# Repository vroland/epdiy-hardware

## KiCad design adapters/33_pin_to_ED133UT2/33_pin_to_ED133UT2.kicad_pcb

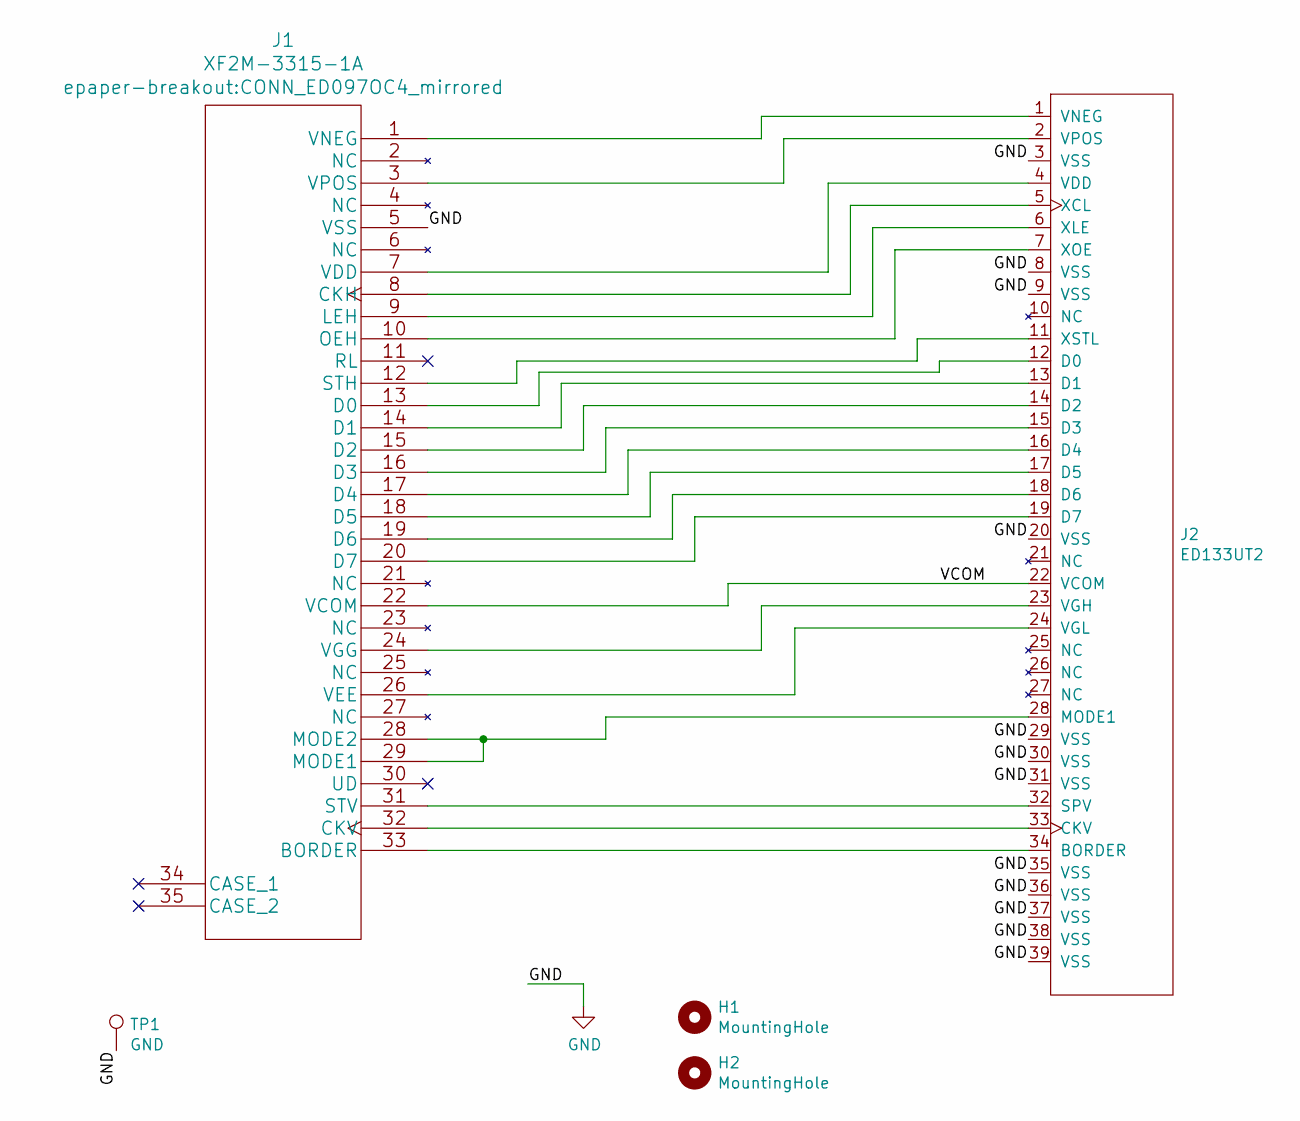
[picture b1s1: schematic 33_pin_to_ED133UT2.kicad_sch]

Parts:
H1, H2: MountingHole; MountingHole_2.2mm_M2
J1: XF2M-3315-1A; CONN_ED097OC4_mirrored
J2: ED133UT2; HRS_FH26W-39S-0.3SHW(60)
TP1: GND; TestPoint_Pad_D2.0mm

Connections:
/VCOM: J1.22 (VCOM), J2.22 (VCOM)
GND: J1.5 (VSS), J2.3 (VSS), J2.8 (VSS), J2.9 (VSS), J2.20 (VSS), J2.29 (VSS), J2.30 (VSS), J2.31 (VSS), J2.35 (VSS), J2.36 (VSS), J2.37 (VSS), J2.38 (VSS), J2.39 (VSS), TP1.1
unnamed: J1.33 (BORDER), J2.34 (BORDER)
unnamed: J1.8 (CKH), J2.5 (XCL)
unnamed: J1.32 (CKV), J2.33 (CKV)
unnamed: J1.13 (D0), J2.12 (D0)
unnamed: J1.14 (D1), J2.13 (D1)
unnamed: J1.15 (D2), J2.14 (D2)
unnamed: J1.16 (D3), J2.15 (D3)
unnamed: J1.17 (D4), J2.16 (D4)
unnamed: J1.18 (D5), J2.17 (D5)
unnamed: J1.19 (D6), J2.18 (D6)
unnamed: J1.20 (D7), J2.19 (D7)
unnamed: J1.9 (LEH), J2.6 (XLE)
unnamed: J1.28 (MODE2), J1.29 (MODE1), J2.28 (MODE1)
unnamed: J1.10 (OEH), J2.7 (XOE)
unnamed: J1.12 (STH), J2.11 (XSTL)
unnamed: J1.31 (STV), J2.32 (SPV)
unnamed: J1.7 (VDD), J2.4 (VDD)
unnamed: J1.26 (VEE), J2.24 (VGL)
unnamed: J1.24 (VGG), J2.23 (VGH)
unnamed: J1.1 (VNEG), J2.1 (VNEG)
unnamed: J1.3 (VPOS), J2.2 (VPOS)

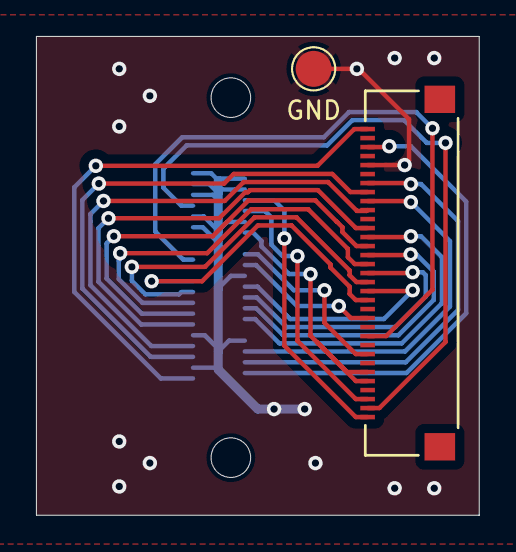
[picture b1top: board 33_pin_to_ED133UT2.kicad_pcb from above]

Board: 2 copper layers, 24.6 x 26.6 mm, 5 parts (1 on the bottom side), 23 nets.

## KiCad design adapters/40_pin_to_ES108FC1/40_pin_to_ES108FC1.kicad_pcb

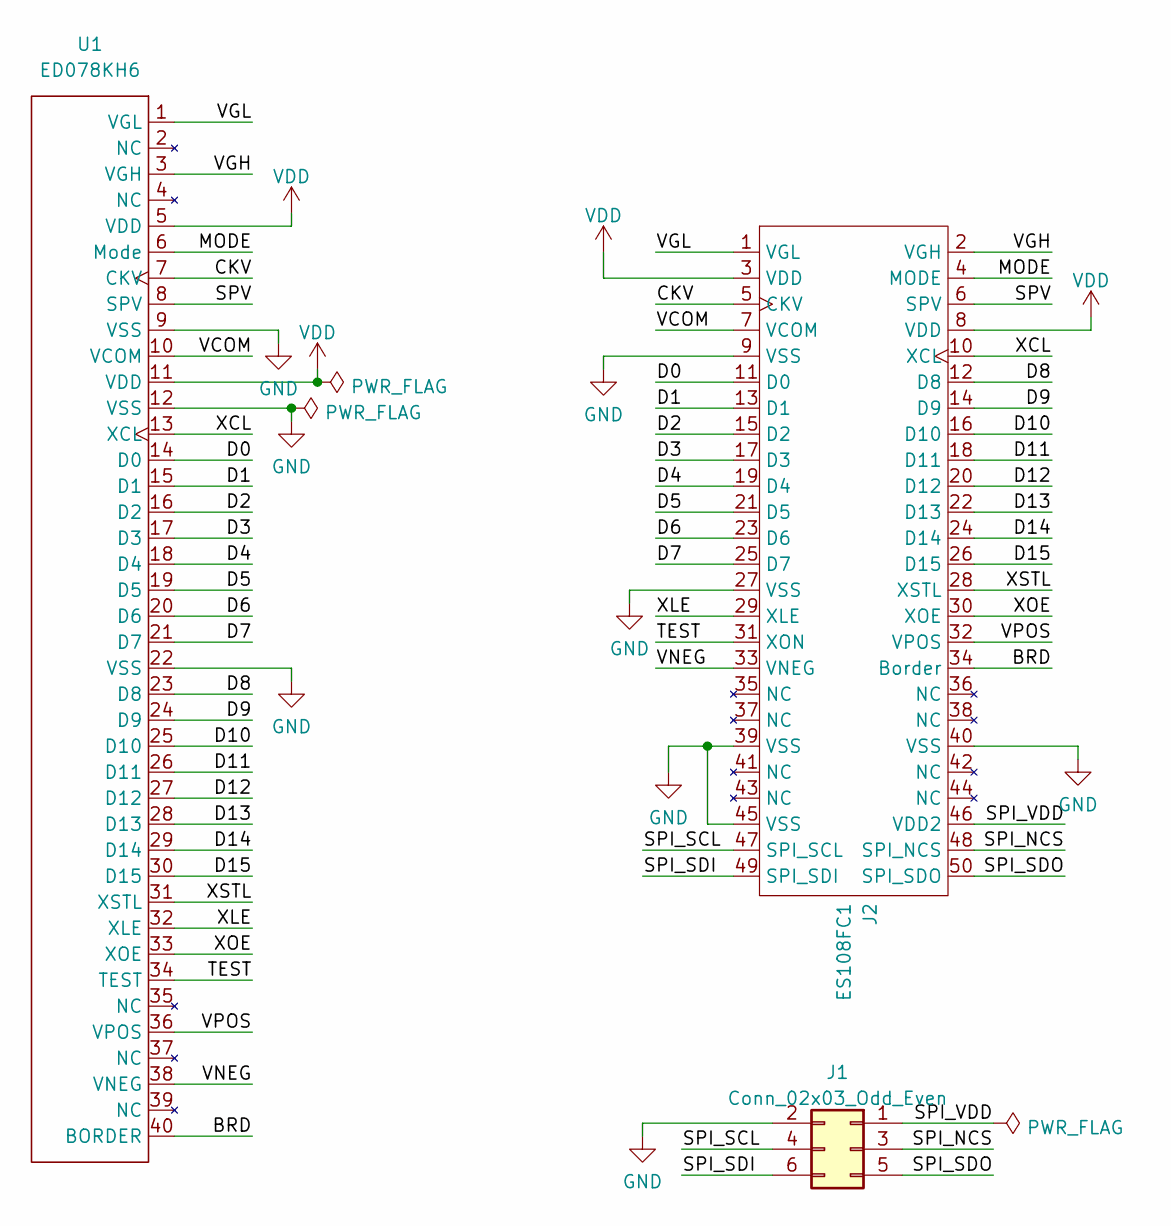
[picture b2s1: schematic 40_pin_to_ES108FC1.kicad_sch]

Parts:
J1: Conn_02x03_Odd_Even; PinHeader_2x03_P2.54mm_Vertical
J2: ES108FC1; LCSC C2880696
U1: ED078KH6; Hirose_FH12-40S-0.5SH_mirrored; LCSC C202114

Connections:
/BRD: J2.34 (Border), U1.40 (BORDER)
/CKV: J2.5 (CKV), U1.7 (CKV)
/D0: J2.11 (D0), U1.14 (D0)
/D1: J2.13 (D1), U1.15 (D1)
/D2: J2.15 (D2), U1.16 (D2)
/D3: J2.17 (D3), U1.17 (D3)
/D4: J2.19 (D4), U1.18 (D4)
/D5: J2.21 (D5), U1.19 (D5)
/D6: J2.23 (D6), U1.20 (D6)
/D7: J2.25 (D7), U1.21 (D7)
/D8: J2.12 (D8), U1.23 (D8)
/D9: J2.14 (D9), U1.24 (D9)
/D10: J2.16 (D10), U1.25 (D10)
/D11: J2.18 (D11), U1.26 (D11)
/D12: J2.20 (D12), U1.27 (D12)
/D13: J2.22 (D13), U1.28 (D13)
/D14: J2.24 (D14), U1.29 (D14)
/D15: J2.26 (D15), U1.30 (D15)
/MODE: J2.4 (MODE), U1.6 (Mode)
/SPI_NCS: J1.3, J2.48 (SPI_NCS)
/SPI_SCL: J1.4, J2.47 (SPI_SCL)
/SPI_SDI: J1.6, J2.49 (SPI_SDI)
/SPI_SDO: J1.5, J2.50 (SPI_SDO)
/SPI_VDD: J1.1, J2.46 (VDD2)
/SPV: J2.6 (SPV), U1.8 (SPV)
/TEST: J2.31 (XON), U1.34 (TEST)
/VCOM: J2.7 (VCOM), U1.10 (VCOM)
/VGH: J2.2 (VGH), U1.3 (VGH)
/VGL: J2.1 (VGL), U1.1 (VGL)
/VNEG: J2.33 (VNEG), U1.38 (VNEG)
/VPOS: J2.32 (VPOS), U1.36 (VPOS)
/XCL: J2.10 (XCL), U1.13 (XCL)
/XLE: J2.29 (XLE), U1.32 (XLE)
/XOE: J2.30 (XOE), U1.33 (XOE)
/XSTL: J2.28 (XSTL), U1.31 (XSTL)
GND: J1.2, J2.9 (VSS), J2.27 (VSS), J2.39 (VSS), J2.40 (VSS), J2.45 (VSS), U1.9 (VSS), U1.12 (VSS), U1.22 (VSS)
VDD: J2.3 (VDD), J2.8 (VDD), U1.5 (VDD), U1.11 (VDD)

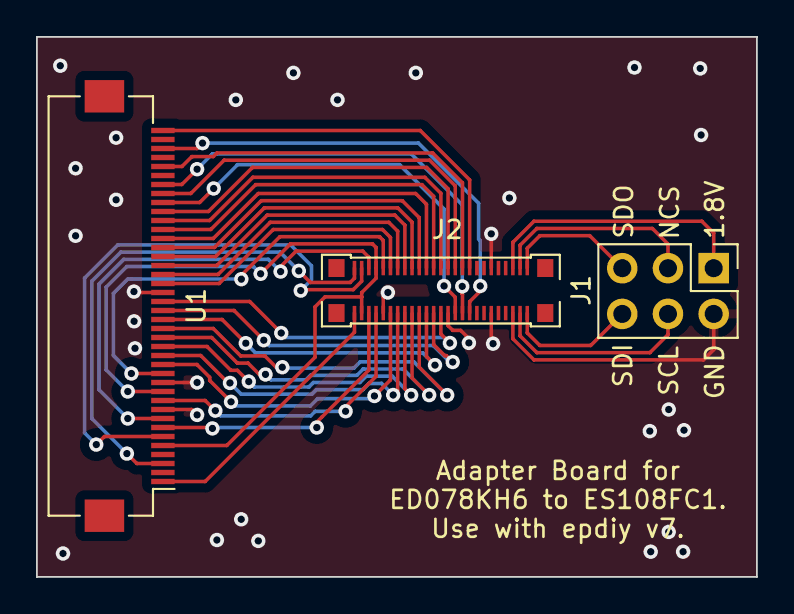
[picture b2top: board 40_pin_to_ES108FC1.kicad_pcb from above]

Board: 2 copper layers, 40.0 x 30.0 mm, 3 parts (0 on the bottom side), 37 nets.

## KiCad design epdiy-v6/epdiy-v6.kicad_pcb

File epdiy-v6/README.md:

### Epdiy V6

Uses the TPS65185 IC for power delivery instead of the previous design and drops the ED060SC7 connector,
but adds additional available GPIOs though a GPIO expander.

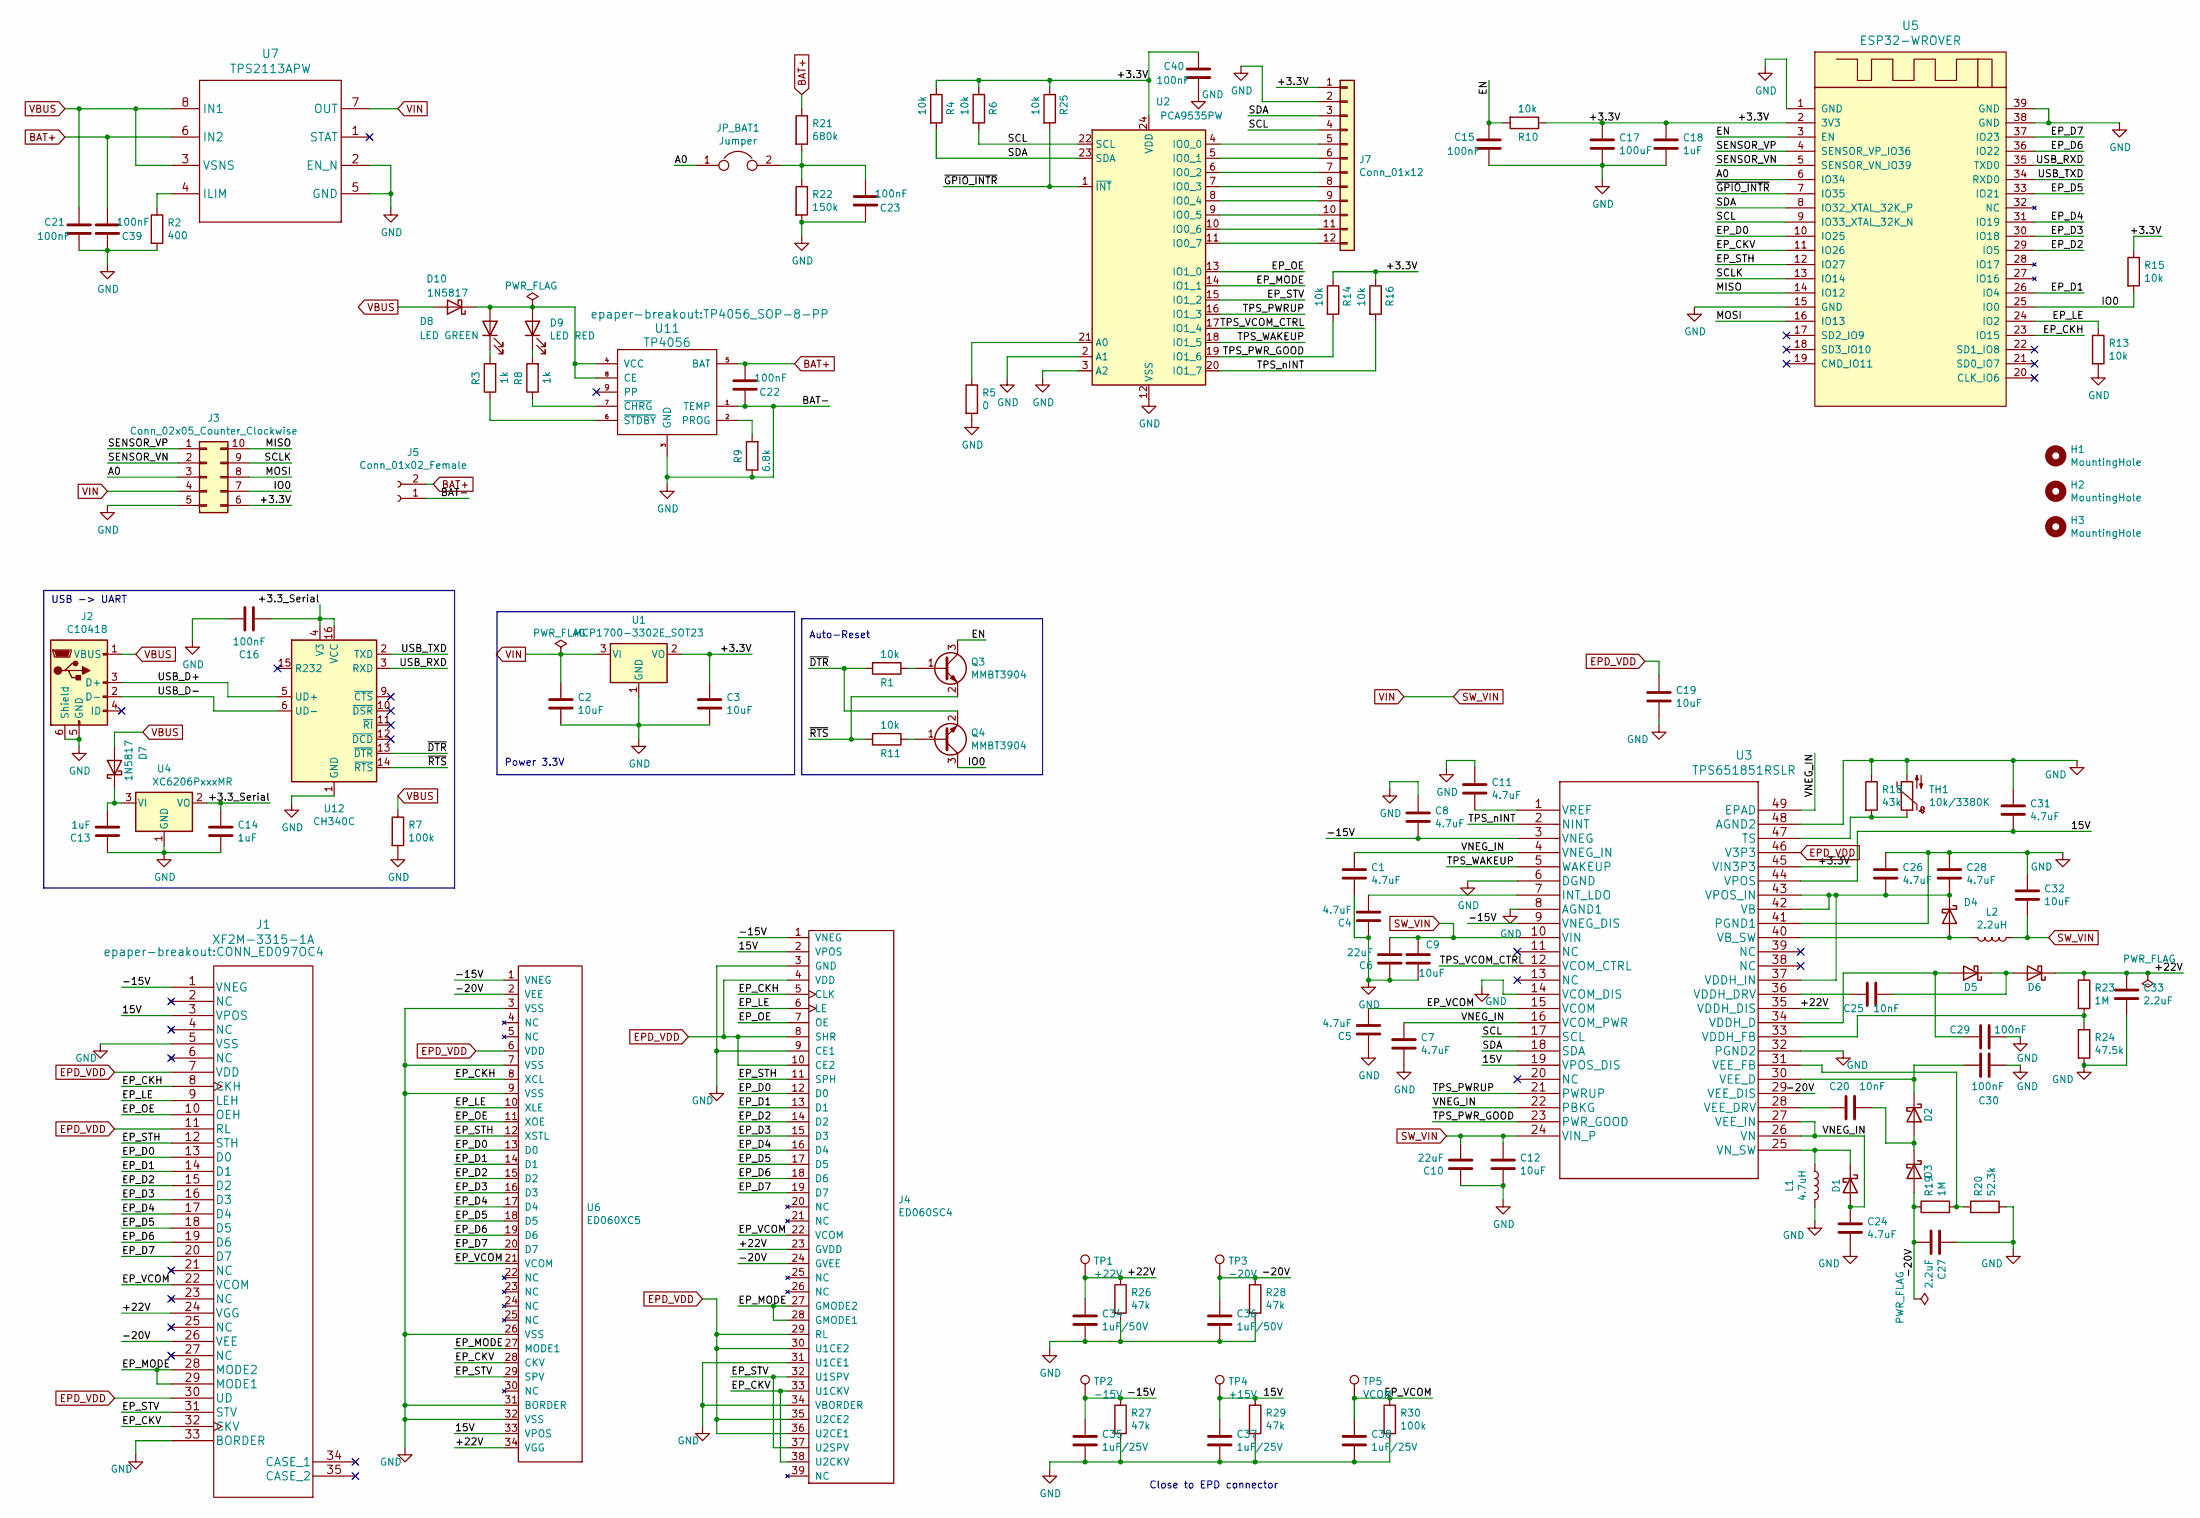
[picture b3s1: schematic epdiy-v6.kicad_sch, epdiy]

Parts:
C1, C4, C5, C7, C8, C11, C24, C26, C28, C31: 4.7uF; C_0805_2012Metric; LCSC C1779
C2, C3, C9, C12, C32: 10uF; C_0805_2012Metric; LCSC C15850
C6, C10: 22uF; C_0805_2012Metric; LCSC C45783
C13, C14, C18: 1uF; C_0805_2012Metric; LCSC C28323
C15, C16, C21, C22, C23, C29, C30, C39, C40: 100nF; C_0805_2012Metric; LCSC C49678
C17: 100uF; CP_EIA-3528-15_AVX-H; LCSC C16133
C19: 10uF; C_0805_2012Metric; LCSC C19702
C20, C25: 10nF; C_0805_2012Metric; LCSC C1710
C27, C33: 2.2uF; C_0805_2012Metric; LCSC C49217
C34, C36: 1uF/50V; C_1206_3216Metric; LCSC C1848
C35, C37, C38: 1uF/25V; C_0805_2012Metric; LCSC C28323
D1, D2, D3, D4, D5, D6: MBR0540; D_SOD-123; LCSC C21353
D7, D10: 1N5817; D_SOD-123; LCSC C8598
D8: LED GREEN; LED_0805_2012Metric; LCSC C2297
D9: LED RED; LED_0805_2012Metric; LCSC C84256
H1, H2, H3: MountingHole; MountingHole_2.2mm_M2
J1: XF2M-3315-1A; CONN_ED097OC4; LCSC C231420
J2: C10418; USB_Micro-B_A01SB141B1-067; LCSC C10418
J3: Conn_02x05_Counter_Clockwise; PinHeader_2x05_P2.54mm_Vertical
J4: ED060SC4; HRS_FH26W-39S-0.3SHW(60); LCSC C519255
J5: Conn_01x02_Female; PinHeader_1x02_P2.54mm_Vertical
J7: Conn_01x12; PinHeader_2x06_P2.54mm_Vertical
JP_BAT1: Jumper; SolderJumper-2_P1.3mm_Bridged2Bar_RoundedPad1.0x1.5mm
L1: 4.7uH; L_Taiyo-Yuden_NR-50xx_HandSoldering; LCSC C222947
L2: 2.2uH; L_Taiyo-Yuden_NR-40xx_HandSoldering; LCSC C92959
Q3, Q4: MMBT3904; SOT-23; LCSC C20526
R1, R4, R6, R10, R11, R13, R14, R15, R16, R25: 10k; R_0603_1608Metric; LCSC C25804
R2: 400; R_0603_1608Metric; LCSC C23151
R3, R8: 1k; R_0603_1608Metric; LCSC C21190
R5: 0; R_0603_1608Metric
R7, R30: 100k; R_0603_1608Metric; LCSC C25803
R9: 6.8k; R_0603_1608Metric; LCSC C23212
R18: 43k; R_0603_1608Metric; LCSC C23172
R19, R23: 1M; R_0603_1608Metric; LCSC C22935
R20: 52.3k; R_0603_1608Metric; LCSC C23196
R21: 680k; R_0603_1608Metric; LCSC C25822
R22: 150k; R_0603_1608Metric; LCSC C22807
R24: 47.5k; R_0603_1608Metric; LCSC C25819
R26, R27, R28, R29: 47k; R_0603_1608Metric; LCSC C25819
TH1: 10k/3380K; R_0603_1608Metric; LCSC C76589
TP1: +22V; TestPoint_Pad_D2.5mm
TP2: -15V; TestPoint_Pad_D2.5mm
TP3: -20V; TestPoint_Pad_D2.5mm
TP4: +15V; TestPoint_Pad_D2.5mm
TP5: VCOM; TestPoint_Pad_D2.5mm
U1: MCP1700-3302E_SOT23; SOT-23; LCSC C39051
U2: PCA9535PW; TSSOP-24_4.4x7.8mm_P0.65mm; LCSC C255606
U3: TPS651851RSLR; LCSC C139292
U4: XC6206PxxxMR; SOT-23; LCSC C5446
U5: ESP32-WROVER; LCSC C503591
U6: ED060XC5; X05A20H34G; LCSC C528053
U7: TPS2113APW; LCSC C130052
U11: TP4056; TP4056_SOP-8-PP; LCSC C16581
U12: CH340C; SOIC-16_3.9x9.9mm_P1.27mm; LCSC C84681

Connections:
/15V: C31.2, C37.1, J1.3 (VPOS), J4.2 (VPOS), R29.1, TP4.1, U3.19 (VPOS_DIS), U3.44 (VPOS), U6.33 (VPOS)
/+3.3V: C3.2, C17.1, C18.2, C40.1, J3.6, J7.1, R4.1, R6.1, R10.1, R14.1, R15.1, R16.1, R25.1, U1.2 (VO), U2.24 (VDD), U3.45 (VIN3P3), U5.2 (3V3)
/+3.3_Serial: C14.2, C16.1, U4.2 (VO), U12.4 (V3), U12.16 (VCC)
/+22V: C33.1, C34.1, D6.1 (K), J1.24 (VGG), J4.23 (GVDD), R23.1, R26.1, TP1.1, U3.35 (VDDH_DIS), U6.34 (VGG)
/-15V: C8.2, C35.1, J1.1 (VNEG), J4.1 (VNEG), R27.1, TP2.1, U3.3 (VNEG), U3.9 (VNEG_DIS), U6.1 (VNEG)
/-20V: C27.2, C36.1, D3.2 (A), J1.26 (VEE), J4.24 (GVEE), R19.1, R28.1, TP3.1, U3.29 (VEE_DIS), U6.2 (VEE)
/A0: J3.3, JP_BAT1.1, U5.6 (IO34)
/EN: C15.1, Q3.3 (C), R10.2, U5.3 (EN)
/EP_CKH: J1.8 (CKH), J4.5 (CLK), U5.23 (IO15), U6.8 (XCL)
/EP_CKV: J1.32 (CKV), J4.33 (U1CKV), J4.38 (U2CKV), U5.11 (IO26), U6.28 (CKV)
/EP_D0: J1.13 (D0), J4.12 (D0), U5.10 (IO25), U6.13 (D0)
/EP_D1: J1.14 (D1), J4.13 (D1), U5.26 (IO4), U6.14 (D1)
/EP_D2: J1.15 (D2), J4.14 (D2), U5.29 (IO5), U6.15 (D2)
/EP_D3: J1.16 (D3), J4.15 (D3), U5.30 (IO18), U6.16 (D3)
/EP_D4: J1.17 (D4), J4.16 (D4), U5.31 (IO19), U6.17 (D4)
/EP_D5: J1.18 (D5), J4.17 (D5), U5.33 (IO21), U6.18 (D5)
/EP_D6: J1.19 (D6), J4.18 (D6), U5.36 (IO22), U6.19 (D6)
/EP_D7: J1.20 (D7), J4.19 (D7), U5.37 (IO23), U6.20 (D7)
/EP_LE: J1.9 (LEH), J4.6 (LE), R13.1, U5.24 (IO2), U6.10 (XLE)
/EP_MODE: J1.28 (MODE2), J1.29 (MODE1), J4.27 (GMODE2), J4.28 (GMODE1), U2.14 (IO1_1), U6.27 (MODE1)
/EP_OE: J1.10 (OEH), J4.7 (OE), U2.13 (IO1_0), U6.11 (XOE)
/EP_STH: J1.12 (STH), J4.11 (SPH), U5.12 (IO27), U6.12 (XSTL)
/EP_STV: J1.31 (STV), J4.32 (U1SPV), J4.37 (U2SPV), U2.15 (IO1_2), U6.29 (SPV)
/EP_VCOM: C5.2, C38.1, J1.22 (VCOM), J4.22 (VCOM), R30.1, TP5.1, U3.15 (VCOM), U6.21 (VCOM)
/IO0: J3.7, Q4.3 (C), R15.2, U5.25 (IO0)
/MISO: J3.10, U5.14 (IO12)
/MOSI: J3.8, U5.16 (IO13)
/SCL: J7.4, R6.2, U2.22 (SCL), U3.17 (SCL), U5.9 (IO33_XTAL_32K_N)
/SCLK: J3.9, U5.13 (IO14)
/SDA: J7.3, R4.2, U2.23 (SDA), U3.18 (SDA), U5.8 (IO32_XTAL_32K_P)
/SENSOR_VN: J3.2, U5.5 (SENSOR_VN_IO39)
/SENSOR_VP: J3.1, U5.4 (SENSOR_VP_IO36)
/TPS_PWRUP: U2.16 (IO1_3), U3.21 (PWRUP)
/TPS_PWR_GOOD: R14.2, U2.19 (IO1_6), U3.23 (PWR_GOOD)
/TPS_VCOM_CTRL: U2.17 (IO1_4), U3.12 (VCOM_CTRL)
/TPS_WAKEUP: U2.18 (IO1_5), U3.5 (WAKEUP)
/TPS_nINT: R16.2, U2.20 (IO1_7), U3.2 (NINT)
/USB_D+: J2.3 (D+), U12.5 (UD+)
/USB_D-: J2.2 (D-), U12.6 (UD-)
/USB_RXD: U5.35 (TXD0), U12.3 (RXD)
/USB_TXD: U5.34 (RXD0), U12.2 (TXD)
/VNEG_IN: C1.1, C7.1, C24.1, D1.2 (A), U3.4 (VNEG_IN), U3.16 (VCOM_PWR), U3.22 (PBKG), U3.26 (VN), U3.27 (VEE_IN), U3.49 (EPAD)
/~DTR: Q4.2 (E), R1.2, U12.13 (~DTR)
/~GPIO_INTR: R25.2, U2.1 (~INT), U5.7 (IO35)
/~RTS: Q3.2 (E), R11.2, U12.14 (~RTS)
BAT+: C22.2, C39.2, J5.2, R21.1, U7.6 (IN2), U11.5 (BAT)
EPD_VDD: C19.1, J1.7 (VDD), J1.11 (RL), J1.30 (UD), J4.4 (VDD), J4.8 (SHR), J4.10 (CE2), J4.29 (RL), J4.30 (U1CE2), J4.35 (U2CE2), J4.36 (U2CE1), U3.46 (V3P3), U6.6 (VDD)
GND: C1.2, C2.1, C3.1, C4.1, C5.1, C6.1, C7.2, C8.1, C9.2, C10.1, C11.1, C12.2, C13.2, C14.1, C15.2, C16.2, C17.2, C18.1, C19.2, C21.2, C22.1, C23.1, C24.2, C26.1, C27.1, C28.1, C29.1, C30.2, C31.1, C32.1, C33.2, C34.2, C35.2, C36.2, C37.2, C38.2, C39.1, C40.2, J1.5 (VSS), J1.33 (BORDER), J2.5 (GND), J2.6 (Shield), J3.5, J4.3 (GND), J4.9 (CE1), J4.31 (U1CE1), J4.34 (VBORDER), J5.1, J7.2, L1.2, R2.2, R5.2, R7.2, R9.1, R13.2, R18.1, R20.2, R22.2, R24.2, R26.2, R27.2, R28.2, R29.2, R30.2, TH1.2, U1.1 (GND), U2.2 (A1), U2.3 (A2), U2.12 (VSS), U3.6 (DGND), U3.8 (AGND1), U3.14 (VCOM_DIS), U3.32 (PGND2), U3.41 (PGND1), U3.48 (AGND2), U4.1 (GND), U5.1 (GND), U5.15 (GND), U5.38 (GND), U5.39 (GND), U6.3 (VSS), U6.7 (VSS), U6.9 (VSS), U6.26 (VSS), U6.31 (BORDER), U6.32 (VSS), U7.2 (EN_N), U7.5 (GND), U11.1 (TEMP), U11.3 (GND), U12.1 (GND)
unnamed: C23.2, JP_BAT1.2, R21.2, R22.1
unnamed: D1.1 (K), L1.1, U3.25 (VN_SW)
unnamed: C20.1, D2.2 (A), D3.1 (K)
unnamed: C30.1, D2.1 (K), U3.30 (VEE_D)
unnamed: D4.2 (A), L2.2, U3.40 (VB_SW)
unnamed: C26.2, C28.2, D4.1 (K), U3.37 (VDDH_IN), U3.42 (VB), U3.43 (VPOS_IN)
unnamed: C29.2, D5.2 (A), U3.34 (VDDH_D)
unnamed: C25.1, D5.1 (K), D6.2 (A)
unnamed: C13.1, D7.1 (K), U4.3 (VI)
unnamed: D8.1 (K), R3.2
unnamed: D9.1 (K), R8.2
unnamed: D8.2 (A), D9.2 (A), D10.1 (K), U11.4 (VCC), U11.8 (CE)
unnamed: J7.5, U2.4 (IO0_0)
unnamed: J7.6, U2.5 (IO0_1)
unnamed: J7.7, U2.6 (IO0_2)
unnamed: J7.8, U2.7 (IO0_3)
unnamed: J7.9, U2.8 (IO0_4)
unnamed: J7.10, U2.9 (IO0_5)
unnamed: J7.11, U2.10 (IO0_6)
unnamed: J7.12, U2.11 (IO0_7)
unnamed: Q3.1 (B), R1.1
unnamed: Q4.1 (B), R11.1
unnamed: R5.1, U2.21 (A0)
unnamed: C4.2, U3.7 (INT_LDO)
unnamed: R18.2, TH1.1, U3.47 (TS)
unnamed: C25.2, U3.36 (VDDH_DRV)
unnamed: R23.2, R24.1, U3.33 (VDDH_FB)
unnamed: C20.2, U3.28 (VEE_DRV)
unnamed: R19.2, R20.1, U3.31 (VEE_FB)
unnamed: C11.2, U3.1 (VREF)
unnamed: R2.1, U7.4 (ILIM)
unnamed: R9.2, U11.2 (PROG)
unnamed: R8.1, U11.7 (~CHRG)
unnamed: R3.1, U11.6 (~STDBY)
SW_VIN: C2.2, C6.2, C9.1, C10.2, C12.1, C32.2, J3.4, L2.1, U1.3 (VI), U3.10 (VIN), U3.24 (VIN_P), U7.7 (OUT)
VBUS: C21.1, D7.2 (A), D10.2 (A), J2.1 (VBUS), R7.1, U7.3 (VSNS), U7.8 (IN1)

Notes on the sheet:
Close to EPD connector
Auto-Reset
USB -> UART
Power 3.3V

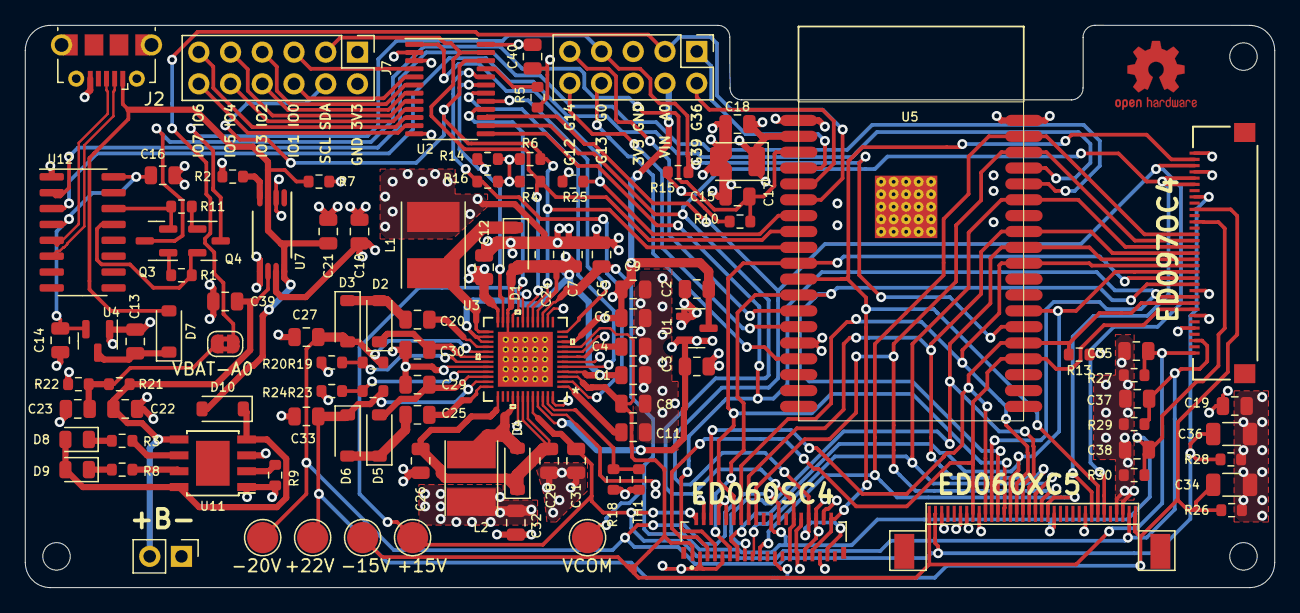
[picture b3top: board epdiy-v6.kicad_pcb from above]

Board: 4 copper layers, 100.0 x 45.0 mm, 108 parts (1 on the bottom side), 84 nets.

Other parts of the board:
CC: Symbol_CreativeCommons_SilkScreenTop_Type2_Big

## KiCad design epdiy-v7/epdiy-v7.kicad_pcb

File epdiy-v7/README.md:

### Epdiy V7

The V7 controller iteration is based on the ESP32S3. Highlights of the new board include:

- Support for high-resolution displays with 16 data lines
- Much faster updates thanks to the ESP32S3 SOC and the LCD peripheral
- An on-board RTC, LiPo charging

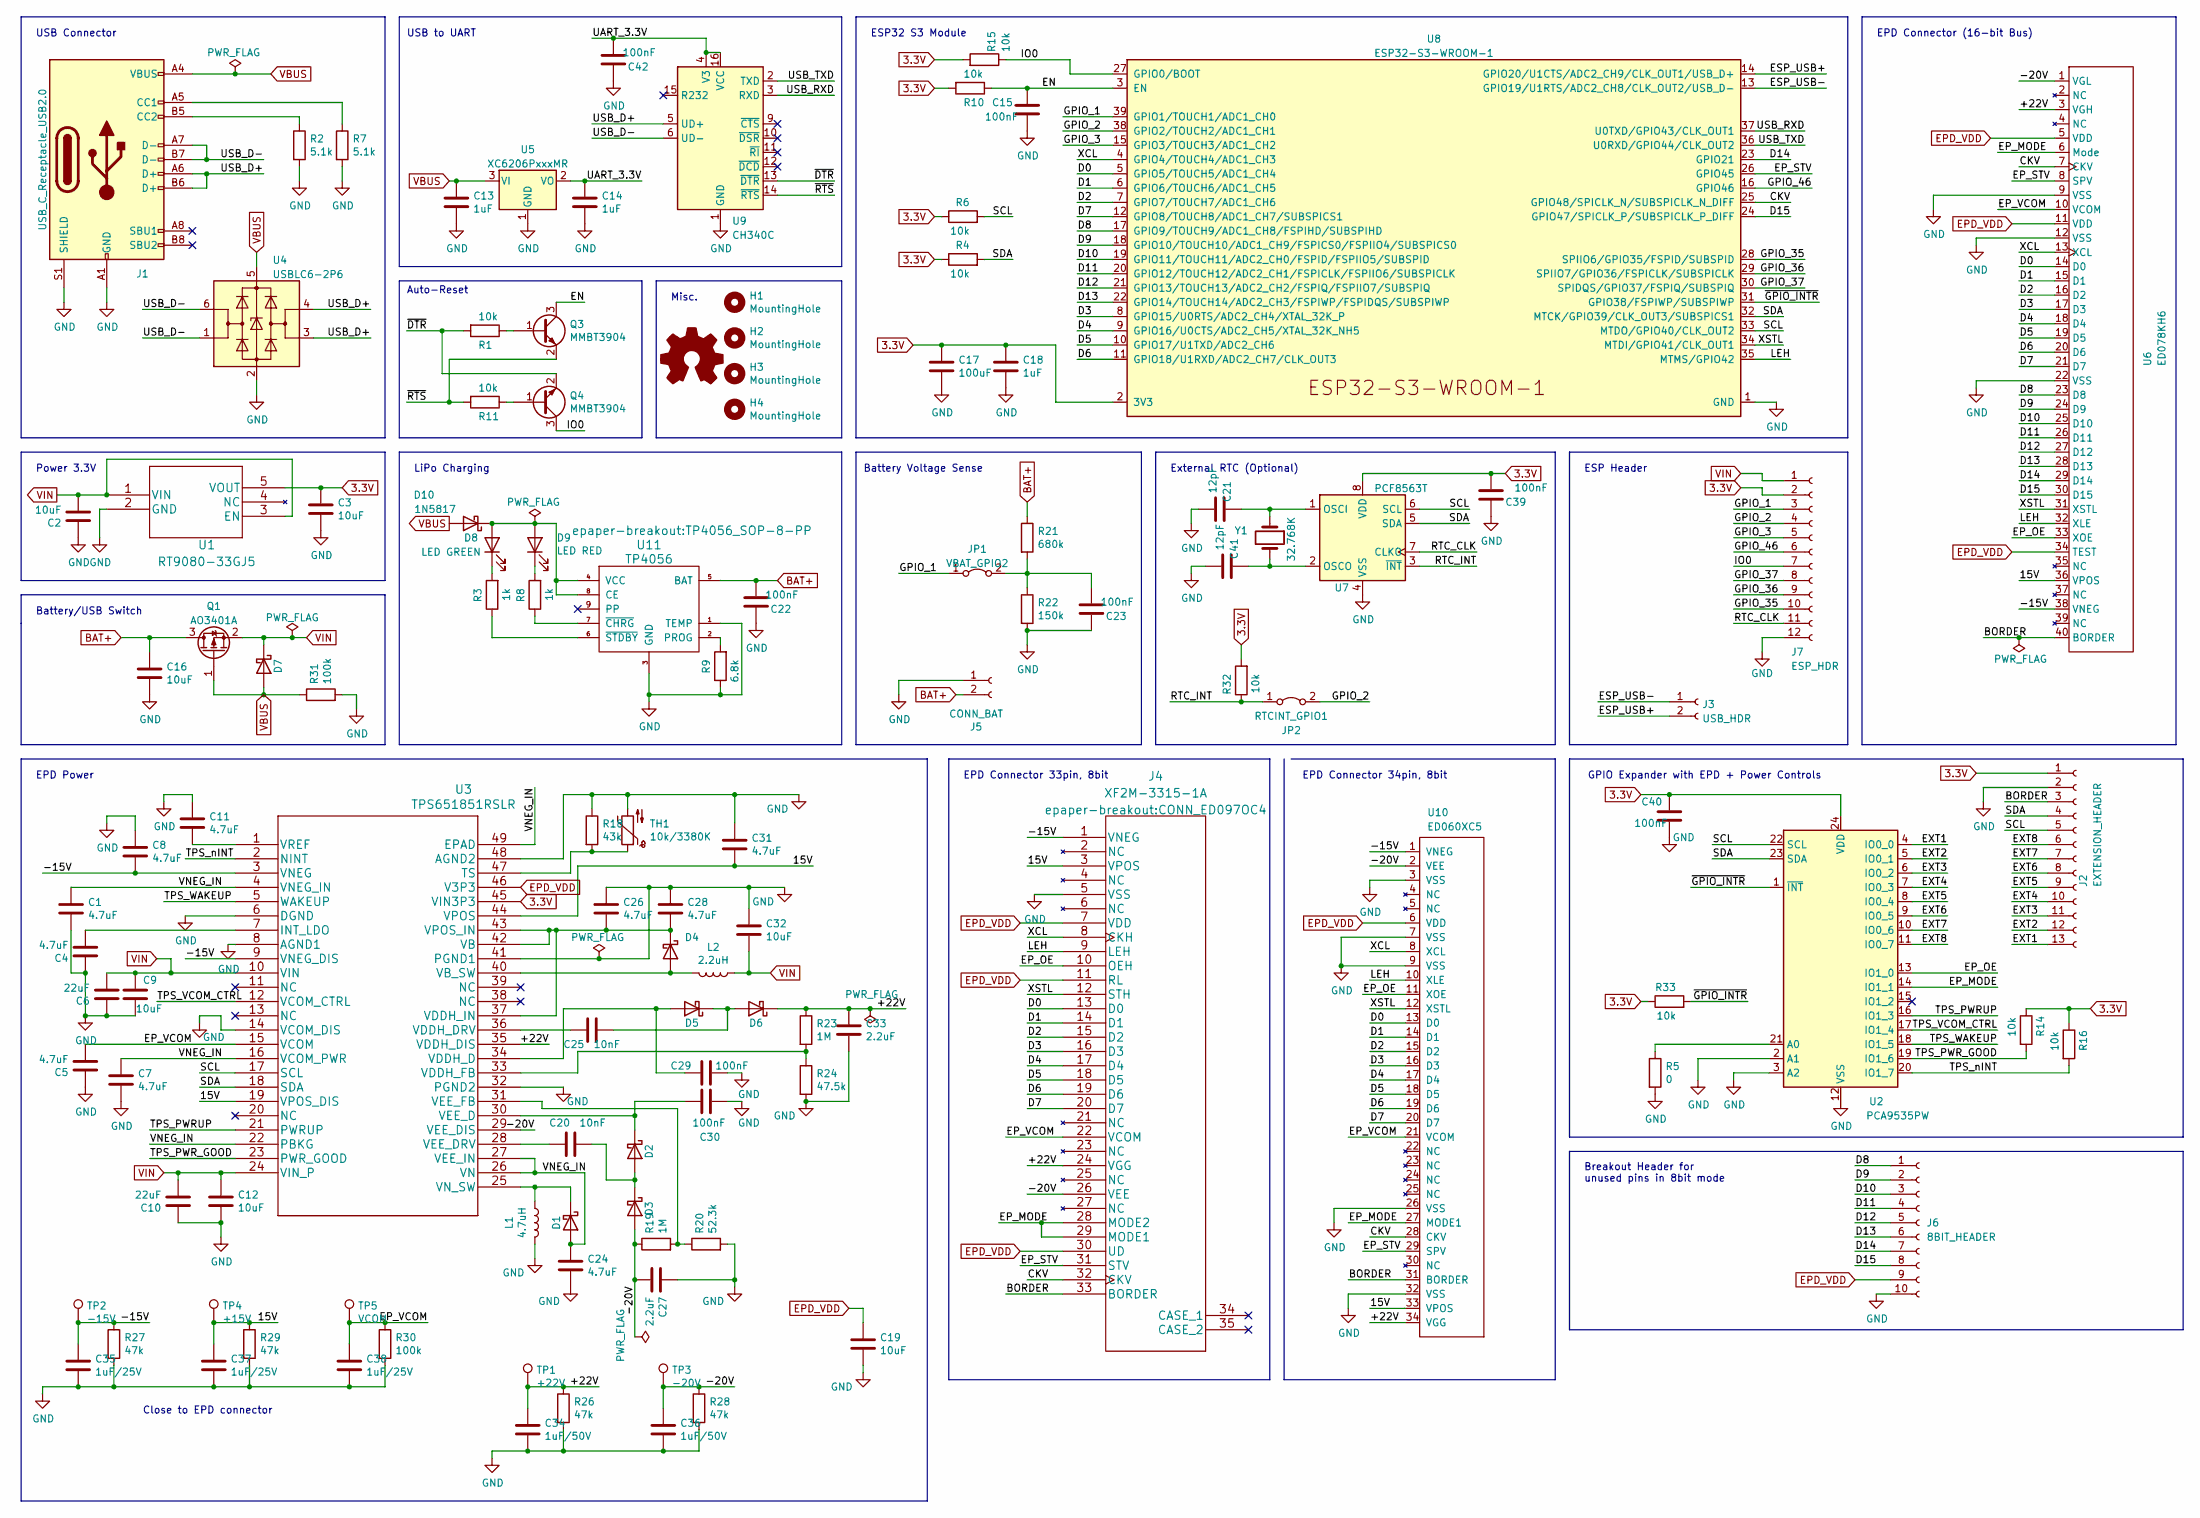
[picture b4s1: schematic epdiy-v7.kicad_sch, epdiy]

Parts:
C1, C4, C5, C7, C8, C11, C24, C26, C28, C31: 4.7uF; C_0805_2012Metric; LCSC C1779
C2, C3, C9, C12, C16, C19, C32: 10uF; C_0805_2012Metric; LCSC C15850
C6, C10: 22uF; C_0805_2012Metric; LCSC C45783
C13, C14, C18: 1uF; C_0805_2012Metric; LCSC C28323
C15, C22, C23, C29, C30, C39, C40, C42: 100nF; C_0805_2012Metric; LCSC C49678
C17: 100uF; CP_EIA-3528-15_AVX-H; LCSC C16133
C20, C25: 10nF; C_0805_2012Metric; LCSC C1710
C21, C41: 12pF; C_0805_2012Metric; LCSC C1792
C27, C33: 2.2uF; C_0805_2012Metric; LCSC C49217
C34, C36: 1uF/50V; C_1206_3216Metric; LCSC C1848
C35, C37, C38: 1uF/25V; C_0805_2012Metric; LCSC C28323
D1, D2, D3, D4, D5, D6, D7: MBR0540; D_SOD-123; LCSC C21353
D8: LED GREEN; LED_0805_2012Metric; LCSC C2297
D9: LED RED; LED_0805_2012Metric; LCSC C84256
D10: 1N5817; D_SOD-123; LCSC C8598
H1, H2, H3, H4: MountingHole; MountingHole_2.2mm_M2
J1: USB_C_Receptacle_USB2.0; USB_C_Receptacle_HRO_TYPE-C-31-M-12; LCSC C165948
J2: EXTENSION_HEADER; PinHeader_1x13_P2.54mm_Vertical
J3: USB_HDR; PinHeader_1x02_P2.54mm_Vertical
J4: XF2M-3315-1A; CONN_ED097OC4; LCSC C231420
J5: CONN_BAT; PinHeader_1x02_P2.54mm_Vertical
J6: 8BIT_HEADER; PinHeader_1x10_P2.54mm_Vertical
J7: ESP_HDR; PinHeader_1x12_P2.54mm_Vertical
JP1: VBAT_GPIO2; SolderJumper-2_P1.3mm_Bridged2Bar_Pad1.0x1.5mm
JP2: RTCINT_GPIO1; SolderJumper-2_P1.3mm_Bridged2Bar_Pad1.0x1.5mm
L1: 4.7uH; L_Taiyo-Yuden_NR-50xx_HandSoldering; LCSC C222947
L2: 2.2uH; L_Taiyo-Yuden_NR-40xx_HandSoldering; LCSC C92959
Q1: AO3401A; SOT-23; LCSC C15127
Q3, Q4: MMBT3904; SOT-23; LCSC C20526
R1, R4, R6, R10, R11, R14, R15, R16, R32, R33: 10k; R_0603_1608Metric; LCSC C25804
R2, R7: 5.1k; R_0603_1608Metric; LCSC C23186
R3, R8: 1k; R_0603_1608Metric; LCSC C21190
R5: 0; R_0603_1608Metric; LCSC C21189
R9: 6.8k; R_0603_1608Metric; LCSC C23212
R18: 43k; R_0603_1608Metric; LCSC C23172
R19, R23: 1M; R_0603_1608Metric; LCSC C22935
R20: 52.3k; R_0603_1608Metric; LCSC C23196
R21: 680k; R_0603_1608Metric; LCSC C25822
R22: 150k; R_0603_1608Metric; LCSC C22807
R24: 47.5k; R_0603_1608Metric; LCSC C25819
R26, R27, R28, R29: 47k; R_0603_1608Metric; LCSC C25819
R30, R31: 100k; R_0603_1608Metric; LCSC C25803
TH1: 10k/3380K; R_0603_1608Metric; LCSC C76589
TP1: +22V; TestPoint_Pad_D2.5mm
TP2: -15V; TestPoint_Pad_D2.5mm
TP3: -20V; TestPoint_Pad_D2.5mm
TP4: +15V; TestPoint_Pad_D2.5mm
TP5: VCOM; TestPoint_Pad_D2.5mm
U1: RT9080-33GJ5; TSOT-23-5; LCSC C841192
U2: PCA9535PW; TSSOP-24_4.4x7.8mm_P0.65mm; LCSC C255606
U3: TPS651851RSLR; LCSC C139292
U4: USBLC6-2P6; SOT-666; LCSC C2827693
U5: XC6206PxxxMR; SOT-23-3; LCSC C5446
U6: ED078KH6; Hirose_FH12-40S-0.5SH_1x40-1MP_P0.50mm_Horizontal; LCSC C202114
U7: PCF8563T; SOIC-8_3.9x4.9mm_P1.27mm; LCSC C7440
U8: ESP32-S3-WROOM-1; LCSC C2913202
U9: CH340C; SOIC-16_3.9x9.9mm_P1.27mm; LCSC C84681
U10: ED060XC5; X05A20H34G; LCSC C528053
U11: TP4056; TP4056_SOP-8-PP; LCSC C16581
Y1: 32.768K; Crystal_SMD_3215-2Pin_3.2x1.5mm; LCSC C32346

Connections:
3.3V: C3.2, C17.1, C18.2, C39.2, C40.1, J2.1, J7.2, R4.1, R6.1, R10.2, R14.1, R15.2, R16.1, R32.2, R33.1, U1.5 (VOUT), U2.24 (VDD), U3.45 (VIN3P3), U7.8 (VDD), U8.2 (3V3)
/15V: C31.2, C37.1, J4.3 (VPOS), R29.1, TP4.1, U3.19 (VPOS_DIS), U3.44 (VPOS), U6.36 (VPOS), U10.33 (VPOS)
/+22V: C33.1, C34.1, D6.1 (K), J4.24 (VGG), R23.1, R26.1, TP1.1, U3.35 (VDDH_DIS), U6.3 (VGH), U10.34 (VGG)
/-15V: C8.2, C35.1, J4.1 (VNEG), R27.1, TP2.1, U3.3 (VNEG), U3.9 (VNEG_DIS), U6.38 (VNEG), U10.1 (VNEG)
/-20V: C27.2, C36.1, D3.2 (A), J4.26 (VEE), R19.1, R28.1, TP3.1, U3.29 (VEE_DIS), U6.1 (VGL), U10.2 (VEE)
/CKV: J4.32 (CKV), U6.7 (CKV), U8.25 (GPIO48/SPICLK_N/SUBSPICLK_N_DIFF), U10.28 (CKV)
/D0: J4.13 (D0), U6.14 (D0), U8.5 (GPIO5/TOUCH5/ADC1_CH4), U10.13 (D0)
/D1: J4.14 (D1), U6.15 (D1), U8.6 (GPIO6/TOUCH6/ADC1_CH5), U10.14 (D1)
/D2: J4.15 (D2), U6.16 (D2), U8.7 (GPIO7/TOUCH7/ADC1_CH6), U10.15 (D2)
/D3: J4.16 (D3), U6.17 (D3), U8.8 (GPIO15/U0RTS/ADC2_CH4/XTAL_32K_P), U10.16 (D3)
/D4: J4.17 (D4), U6.18 (D4), U8.9 (GPIO16/U0CTS/ADC2_CH5/XTAL_32K_NH5), U10.17 (D4)
/D5: J4.18 (D5), U6.19 (D5), U8.10 (GPIO17/U1TXD/ADC2_CH6), U10.18 (D5)
/D6: J4.19 (D6), U6.20 (D6), U8.11 (GPIO18/U1RXD/ADC2_CH7/CLK_OUT3), U10.19 (D6)
/D7: J4.20 (D7), U6.21 (D7), U8.12 (GPIO8/TOUCH8/ADC1_CH7/SUBSPICS1), U10.20 (D7)
/D8: J6.1, U6.23 (D8), U8.17 (GPIO9/TOUCH9/ADC1_CH8/FSPIHD/SUBSPIHD)
/D9: J6.2, U6.24 (D9), U8.18 (GPIO10/TOUCH10/ADC1_CH9/FSPICS0/FSPIIO4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)
/D10: J6.3, U6.25 (D10), U8.19 (GPIO11/TOUCH11/ADC2_CH0/FSPID/FSPIIO5/S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)
/D11: J6.4, U6.26 (D11), U8.20 (GPIO12/TOUCH12/ADC2_CH1/FSPICLK/FSPIIO6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)
/D12: J6.5, U6.27 (D12), U8.21 (GPIO13/TOUCH13/ADC2_CH2/FSPIQ/FSPIIO7/S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)
/D13: J6.6, U6.28 (D13), U8.22 (GPIO14/TOUCH14/ADC2_CH3/FSPIWP/FSPIDQS/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)
/D14: J6.7, U6.29 (D14), U8.23 (GPIO21)
/D15: J6.8, U6.30 (D15), U8.24 (GPIO47/SPICLK_P/SUBSPICLK_P_DIFF)
/EN: C15.1, Q3.3 (C), R10.1, U8.3 (EN)
/EP_MODE: J4.28 (MODE2), J4.29 (MODE1), U2.14 (IO1_1), U6.6 (Mode), U10.27 (MODE1)
/EP_OE: J4.10 (OEH), U2.13 (IO1_0), U6.33 (XOE), U10.11 (XOE)
/EP_STV: J4.31 (STV), U6.8 (SPV), U8.26 (GPIO45), U10.29 (SPV)
/EP_VCOM: C5.2, C38.1, J4.22 (VCOM), R30.1, TP5.1, U3.15 (VCOM), U6.10 (VCOM), U10.21 (VCOM)
/ESP_USB+: J3.2, U8.14 (GPIO20/U1CTS/ADC2_CH9/CLK_OUT1/USB_D+)
/ESP_USB-: J3.1, U8.13 (GPIO19/U1RTS/ADC2_CH8/CLK_OUT2/USB_D-)
/EXT1: J2.13, U2.4 (IO0_0)
/EXT2: J2.12, U2.5 (IO0_1)
/EXT3: J2.11, U2.6 (IO0_2)
/EXT4: J2.10, U2.7 (IO0_3)
/EXT5: J2.9, U2.8 (IO0_4)
/EXT6: J2.8, U2.9 (IO0_5)
/EXT7: J2.7, U2.10 (IO0_6)
/EXT8: J2.6, U2.11 (IO0_7)
/GPIO_1: J7.3, JP1.1 (A), U8.39 (GPIO1/TOUCH1/ADC1_CH0)
/GPIO_2: J7.4, JP2.2 (B), U8.38 (GPIO2/TOUCH2/ADC1_CH1)
/GPIO_3: J7.5, U8.15 (GPIO3/TOUCH3/ADC1_CH2)
/GPIO_35: J7.10, U8.28 (SPIIO6/GPIO35/FSPID/SUBSPID)
/GPIO_36: J7.9, U8.29 (SPIIO7/GPIO36/FSPICLK/SUBSPICLK)
/GPIO_37: J7.8, U8.30 (SPIDQS/GPIO37/FSPIQ/SUBSPIQ)
/GPIO_46: J7.6, U8.16 (GPIO46)
/IO0: J7.7, Q4.3 (C), R15.1, U8.27 (GPIO0/BOOT)
/LEH: J4.9 (LEH), U6.32 (XLE), U8.35 (MTMS/GPIO42), U10.10 (XLE)
/RTC_CLK: J7.11, U7.7 (CLKO)
/RTC_INT: JP2.1 (A), R32.1, U7.3 (~INT)
/SCL: J2.5, R6.2, U2.22 (SCL), U3.17 (SCL), U7.6 (SCL), U8.33 (MTDO/GPIO40/CLK_OUT2)
/SDA: J2.4, R4.2, U2.23 (SDA), U3.18 (SDA), U7.5 (SDA), U8.32 (MTCK/GPIO39/CLK_OUT3/SUBSPICS1)
/TPS_PWRUP: U2.16 (IO1_3), U3.21 (PWRUP)
/TPS_PWR_GOOD: R14.2, U2.19 (IO1_6), U3.23 (PWR_GOOD)
/TPS_VCOM_CTRL: U2.17 (IO1_4), U3.12 (VCOM_CTRL)
/TPS_WAKEUP: U2.18 (IO1_5), U3.5 (WAKEUP)
/TPS_nINT: R16.2, U2.20 (IO1_7), U3.2 (NINT)
/UART_3.3V: C14.2, C42.2, U5.2 (VO), U9.4 (V3), U9.16 (VCC)
/USB_D+: J1.A6 (D+), J1.B6 (D+), U4.3 (I/O2), U4.4 (I/O2), U9.5 (UD+)
/USB_D-: J1.A7 (D-), J1.B7 (D-), U4.1 (I/O1), U4.6 (I/O1), U9.6 (UD-)
/USB_RXD: U8.37 (U0TXD/GPIO43/CLK_OUT1), U9.3 (RXD)
/USB_TXD: U8.36 (U0RXD/GPIO44/CLK_OUT2), U9.2 (TXD)
/VNEG_IN: C1.1, C7.1, C24.1, D1.2 (A), U3.4 (VNEG_IN), U3.16 (VCOM_PWR), U3.22 (PBKG), U3.26 (VN), U3.27 (VEE_IN), U3.49 (EPAD)
/XCL: J4.8 (CKH), U6.13 (XCL), U8.4 (GPIO4/TOUCH4/ADC1_CH3), U10.8 (XCL)
/XSTL: J4.12 (STH), U6.31 (XSTL), U8.34 (MTDI/GPIO41/CLK_OUT1), U10.12 (XSTL)
/~DTR: Q4.2 (E), R1.2, U9.13 (~DTR)
/~GPIO_INTR: R33.2, U2.1 (~INT), U8.31 (GPIO38/FSPIWP/SUBSPIWP)
/~RTS: Q3.2 (E), R11.2, U9.14 (~RTS)
BAT+: C16.2, C22.2, J5.2, Q1.3 (D), R21.1, U11.5 (BAT)
EPD_VDD: C19.1, J4.7 (VDD), J4.11 (RL), J4.30 (UD), J6.9, U3.46 (V3P3), U6.5 (VDD), U6.11 (VDD), U6.34 (TEST), U10.6 (VDD)
unnamed: D1.1 (K), L1.1, U3.25 (VN_SW)
unnamed: C20.1, D2.2 (A), D3.1 (K)
unnamed: C30.1, D2.1 (K), U3.30 (VEE_D)
unnamed: D4.2 (A), L2.2, U3.40 (VB_SW)
unnamed: C26.2, C28.2, D4.1 (K), U3.37 (VDDH_IN), U3.42 (VB), U3.43 (VPOS_IN)
unnamed: C29.2, D5.2 (A), U3.34 (VDDH_D)
unnamed: C25.1, D5.1 (K), D6.2 (A)
unnamed: D8.1 (K), R3.2
unnamed: D9.1 (K), R8.2
unnamed: D8.2 (A), D9.2 (A), D10.1 (K), U11.4 (VCC), U11.8 (CE)
unnamed: J1.A5 (CC1), R7.1
unnamed: J1.B5 (CC2), R2.1
unnamed: C23.2, JP1.2 (B), R21.2, R22.1
unnamed: Q3.1 (B), R1.1
unnamed: Q4.1 (B), R11.1
unnamed: R5.1, U2.21 (A0)
unnamed: C4.2, U3.7 (INT_LDO)
unnamed: R18.2, TH1.1, U3.47 (TS)
unnamed: C25.2, U3.36 (VDDH_DRV)
unnamed: R23.2, R24.1, U3.33 (VDDH_FB)
unnamed: C20.2, U3.28 (VEE_DRV)
unnamed: R19.2, R20.1, U3.31 (VEE_FB)
unnamed: C11.2, U3.1 (VREF)
unnamed: C21.2, U7.1 (OSCI), Y1.1
unnamed: C41.2, U7.2 (OSCO), Y1.2
unnamed: R9.2, U11.2 (PROG)
unnamed: R8.1, U11.7 (~CHRG)
unnamed: R3.1, U11.6 (~STDBY)
VIN: C2.1, C6.2, C9.1, C10.2, C12.1, C32.2, D7.1 (K), J7.1, L2.1, Q1.2 (S), U1.1 (VIN), U1.3 (EN), U3.10 (VIN), U3.24 (VIN_P)

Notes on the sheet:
Battery Voltage Sense
Misc.
EPD Power
ESP Header
GPIO Expander with EPD + Power Controls
USB Connector
EPD Connector (16-bit Bus)
ESP32 S3 Module
Power 3.3V
Auto-Reset
EPD Connector 33pin, 8bit
Battery/USB Switch
External RTC (Optional)
USB to UART
EPD Connector 34pin, 8bit
Breakout Header for unused pins in 8bit mode
LiPo Charging
Close to EPD connector

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

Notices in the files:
epdiy-v6/epdiy-v6.kicad_sch:
License: CC-BY-SA-4.0
parts and their libraries:
Copyright 2016 Accelerated Designs. All rights reserved.
